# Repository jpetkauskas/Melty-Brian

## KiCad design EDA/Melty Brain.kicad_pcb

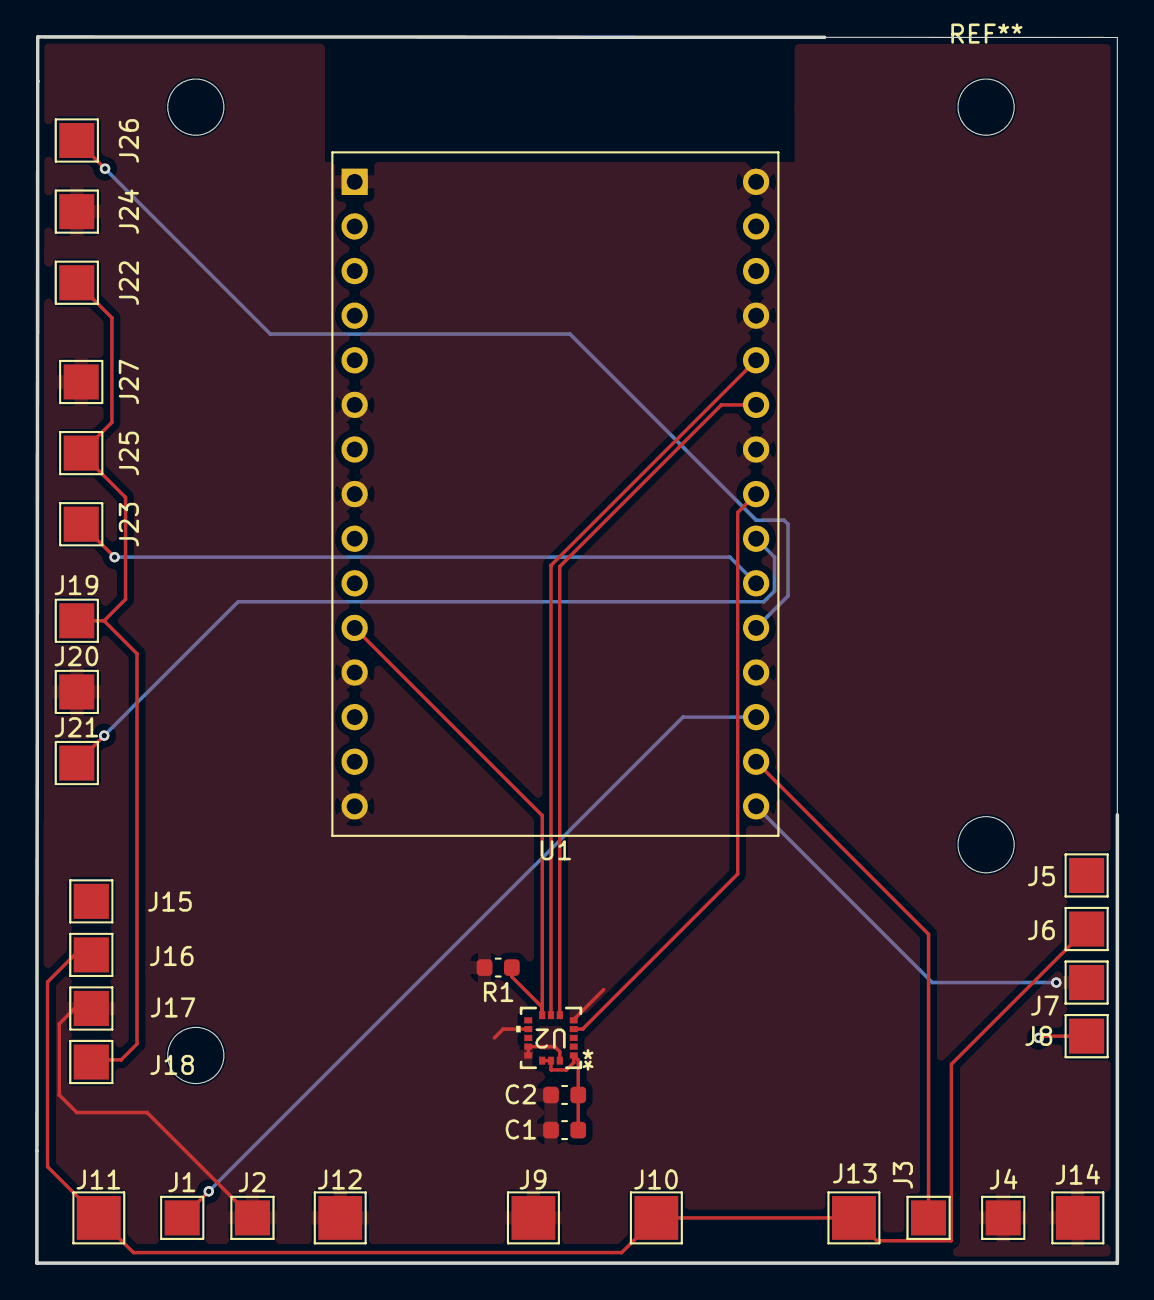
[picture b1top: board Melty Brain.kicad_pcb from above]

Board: 2 copper layers, 61.5 x 69.8 mm, 32 parts (0 on the bottom side), 14 nets.

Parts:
C1: 10uF; C_0603_1608Metric
C2: 100nF; C_0603_1608Metric
J1, J2, J3, J4, J5, J6, J7, J8, J15, J16, J17, J18, J19, J20, J21, J22, J23, J24, J25, J26, J27: Conn_01x01; TestPoint_Pad_2.0x2.0mm
J9, J10, J11, J12, J13, J14: Conn_01x01; TestPoint_Pad_2.5x2.5mm
R1: 10K; C_0603_1608Metric
U1: ESP32-C3-DevKitM-1
U2: H3LIS331DLTR; QFN_31DLTR_STM

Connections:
+3V3: J8.1 (Pin_1_1), U1.2 (3V3), U1.3 (3V3)
GND: C1.2, C2.1, J2.1 (Pin_1_1), J4.1 (Pin_1_1), J7.1 (Pin_1_1), J9.1 (Pin_1_1), J12.1 (Pin_1_1), J14.1 (Pin_1_1), J17.1 (Pin_1_1), J20.1 (Pin_1_1), J24.1 (Pin_1_1), J27.1 (Pin_1_1), R1.2, U1.1 (GND), U1.6 (GND), U1.8 (GND), U1.12 (GND), U1.15 (GND), U1.16 (GND), U1.19 (GND), U1.24 (GND), U1.27 (GND), U1.30 (GND), U2.5 (GND), U2.10 (GND), U2.12 (GND), U2.13 (GND), U2.16 (GND)
unnamed: J1.1 (Pin_1_1), U1.18 (IO18)
unnamed: J3.1 (Pin_1_1), U1.17 (IO19)
unnamed: J6.1 (Pin_1_1), J10.1 (Pin_1_1), J11.1 (Pin_1_1), J13.1 (Pin_1_1), J16.1 (Pin_1_1)
unnamed: J18.1 (Pin_1_1), J19.1 (Pin_1_1), J22.1 (Pin_1_1), J25.1 (Pin_1_1)
unnamed: J21.1 (Pin_1_1), U1.22 (IO6)
unnamed: J23.1 (Pin_1_1), U1.21 (IO5)
unnamed: J26.1 (Pin_1_1), U1.20 (IO4)
unnamed: U1.23 (IO7), U2.4 (SCL/SPC)
unnamed: U1.25 (IO8), U2.6 (SDA/SDI/SDO)
unnamed: U1.26 (IO9), U2.7 (SDO/SA0)
unnamed: R1.1, U1.11 (IO10), U2.8 (CS)
VDD: C1.1, C2.2, U2.1 (VDD_IO), U2.14 (VDD), U2.15 (VDD)

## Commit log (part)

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2026-06-02 Adding EDA
2026-06-02 Reorganize files
